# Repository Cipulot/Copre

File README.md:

# Copre
 40% Topre you can do whatever you want with.

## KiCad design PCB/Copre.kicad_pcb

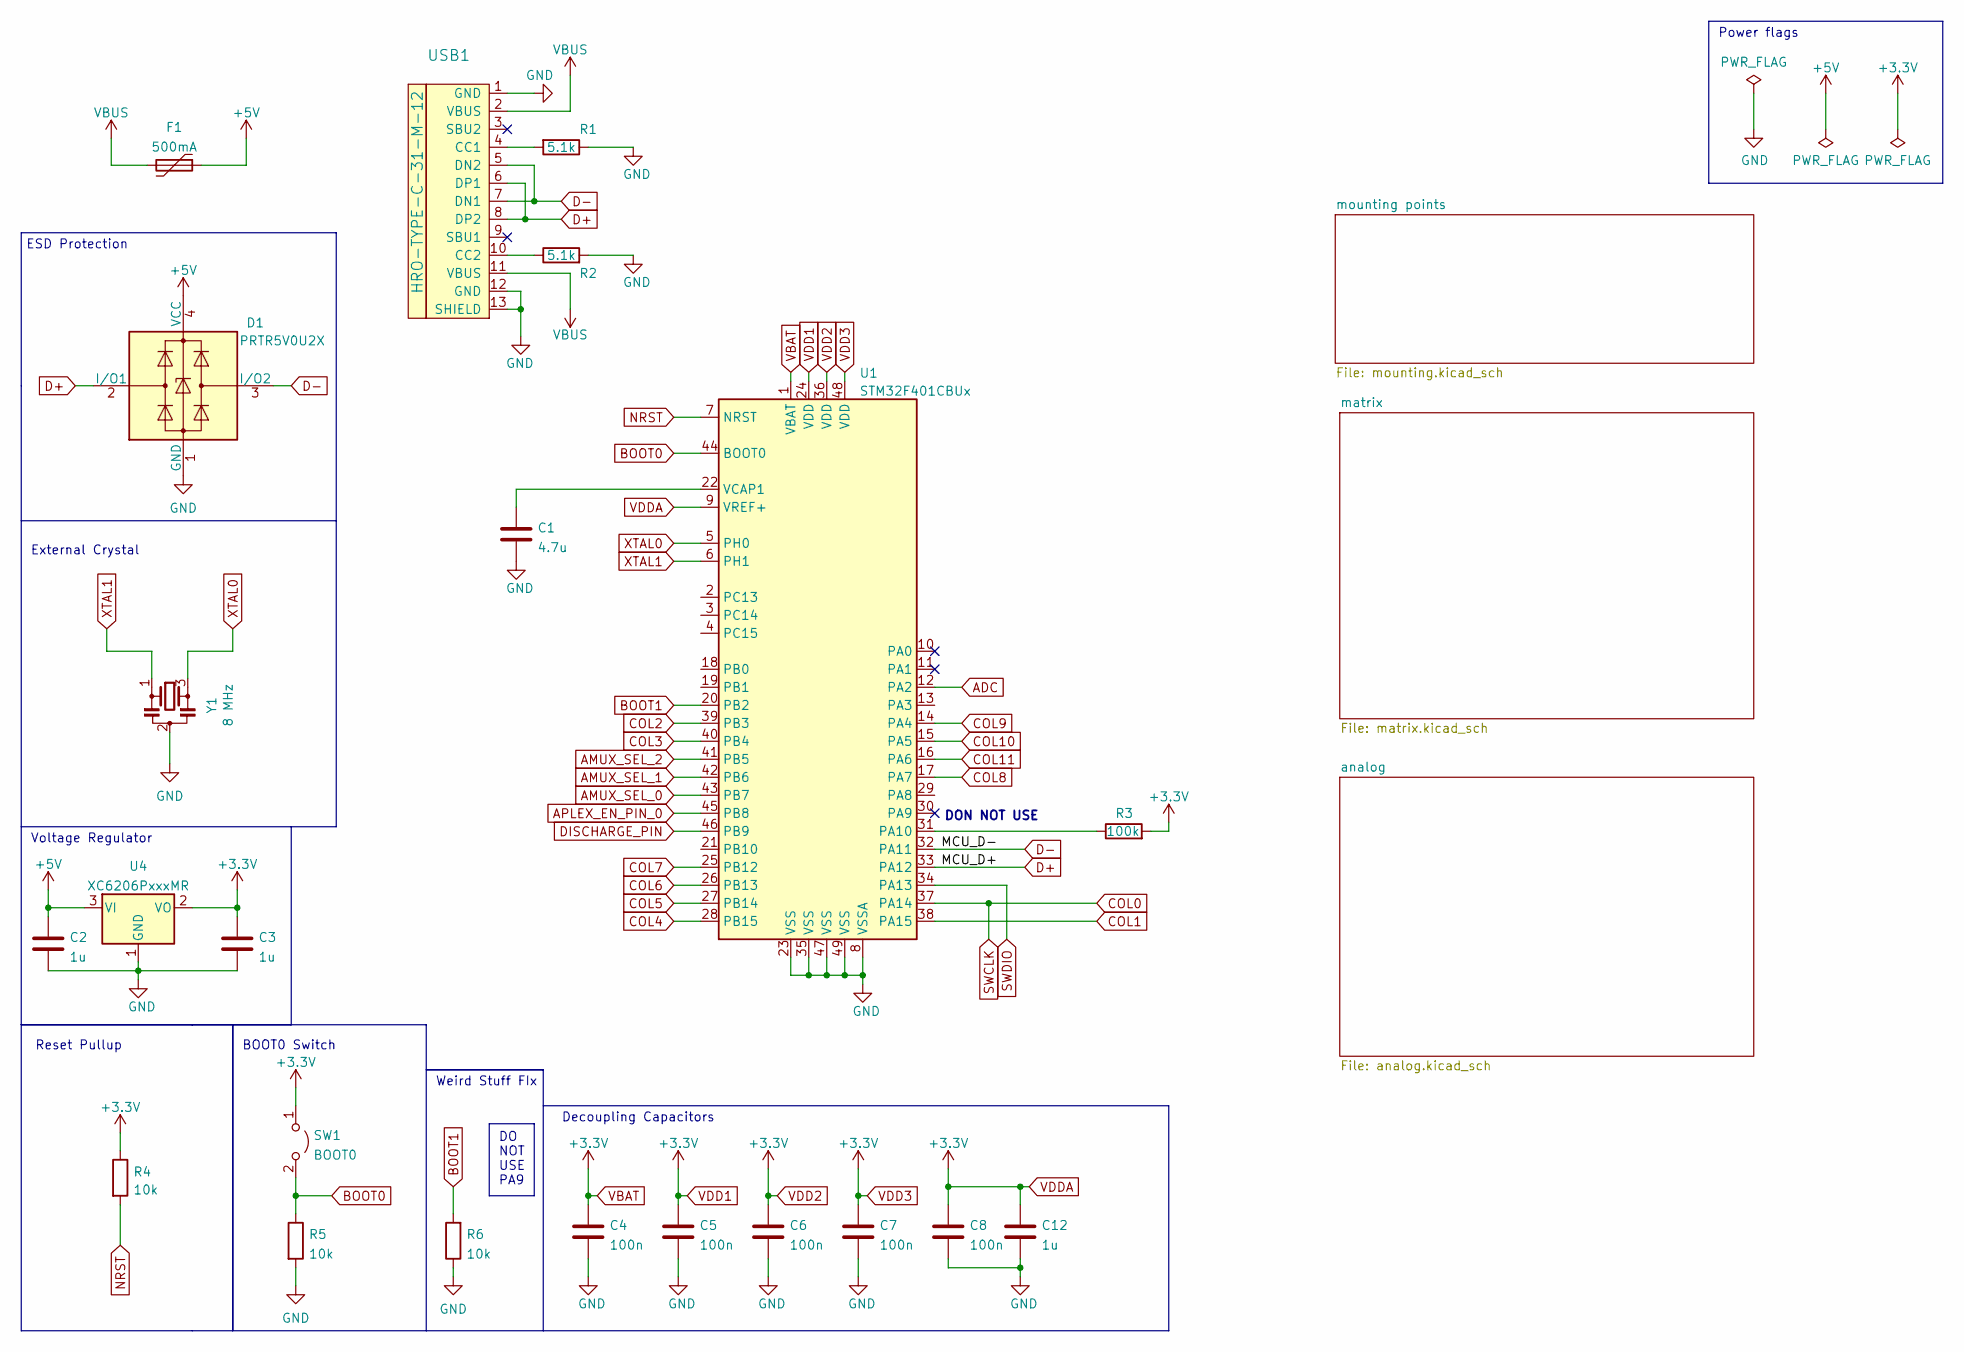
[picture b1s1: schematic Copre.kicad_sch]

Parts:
C1: 4.7u; C_0402_1005Metric; LCSC C23733
C2, C3, C12: 1u; C_0402_1005Metric; LCSC C52923
C4, C5, C6, C7, C8: 100n; C_0402_1005Metric; LCSC C307331
D1: PRTR5V0U2X; SOT-143; LCSC C2827688
F1: 500mA; Fuse_0603_1608Metric; LCSC C720073
R1, R2: 5.1k; R_0402_1005Metric; LCSC C25905
R3: 100k; R_0402_1005Metric; LCSC C25741
R4, R5, R6: 10k; R_0402_1005Metric; LCSC C25744
SW1: BOOT0; JUMPER_SMD_2DUB
U1: STM32F401CBUx; QFN-48-1EP_7x7mm_P0.5mm_EP5.6x5.6mm; LCSC C118825
U4: XC6206PxxxMR; SOT-23; LCSC C5446
USB1: HRO-TYPE-C-31-M-12; HRO-TYPE-C-31-M-12-Assembly
Y1: 8 MHz; Resonator_SMD_Murata_CSTxExxV-3Pin_3.0x1.1mm; LCSC C907975

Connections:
+5V: C2.1, D1.4 (VCC), F1.1, U4.3 (VI)
ADC: U1.12 (PA2); also elsewhere on the board
AMUX_SEL_0: U1.43 (PB7); also elsewhere on the board
AMUX_SEL_1: U1.42 (PB6); also elsewhere on the board
AMUX_SEL_2: U1.41 (PB5); also elsewhere on the board
APLEX_EN_PIN_0: U1.45 (PB8); also elsewhere on the board
APLEX_OUT_PIN_0: U1.46 (PB9); also elsewhere on the board
BOOT0: R5.1, SW1.2 (B), U1.44 (BOOT0)
BOOT1: R6.2, U1.20 (PB2)
COL0: U1.37 (PA14); also elsewhere on the board
COL1: U1.38 (PA15); also elsewhere on the board
COL2: U1.39 (PB3); also elsewhere on the board
COL3: U1.40 (PB4); also elsewhere on the board
COL4: U1.28 (PB15); also elsewhere on the board
COL5: U1.27 (PB14); also elsewhere on the board
COL6: U1.26 (PB13); also elsewhere on the board
COL7: U1.25 (PB12); also elsewhere on the board
COL8: U1.17 (PA7); also elsewhere on the board
COL9: U1.14 (PA4); also elsewhere on the board
COL10: U1.15 (PA5); also elsewhere on the board
COL11: U1.16 (PA6); also elsewhere on the board
D+: D1.2 (I/O1), U1.33 (PA12), USB1.6 (DP1), USB1.8 (DP2)
D-: D1.3 (I/O2), U1.32 (PA11), USB1.5 (DN2), USB1.7 (DN1)
GND: C1.2, C2.2, C3.2, C4.2, C5.2, C6.2, C7.2, C8.2, C12.2, D1.1 (GND), R1.1, R2.2, R5.2, R6.1, U1.8 (VSSA), U1.23 (VSS), U1.35 (VSS), U1.47 (VSS), U1.49 (VSS), U4.1 (GND), USB1.1 (GND), USB1.12 (GND), USB1.13 (SHIELD), Y1.2; also elsewhere on the board
NRST: R4.2, U1.7 (NRST)
unnamed: C1.1, U1.22 (VCAP1)
unnamed: R1.2, USB1.4 (CC1)
unnamed: R2.1, USB1.10 (CC2)
unnamed: R3.1, U1.31 (PA10)
SWDIO: U1.34 (PA13)
VBAT: C3.1, C4.1, C5.1, C6.1, C7.1, C8.1, C12.1, R3.2, R4.1, SW1.1 (A), U1.1 (VBAT), U1.9 (VREF+), U1.24 (VDD), U1.36 (VDD), U1.48 (VDD), U4.2 (VO); also elsewhere on the board
VBUS: F1.2, USB1.2 (VBUS), USB1.11 (VBUS)
XTAL0: U1.5 (PH0), Y1.3
XTAL1: U1.6 (PH1), Y1.1

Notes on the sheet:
DO NOT USE PA9
Voltage Regulator
DON NOT USE
BOOT0 Switch
External Crystal
Weird Stuff FIx
Decoupling Capacitors
Power flags
ESD Protection
Reset Pullup

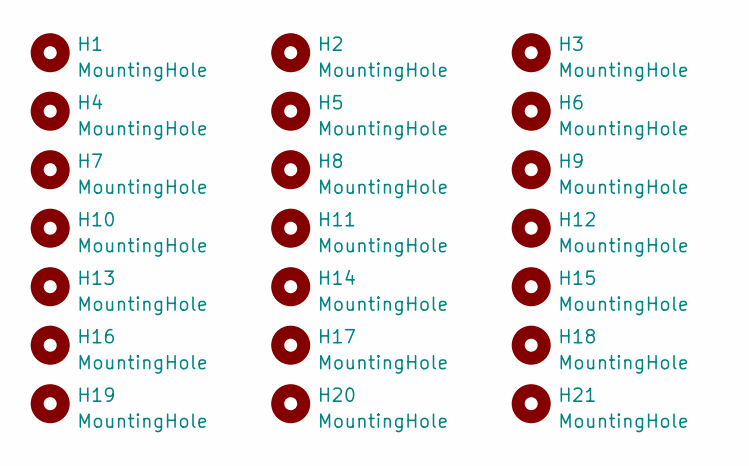
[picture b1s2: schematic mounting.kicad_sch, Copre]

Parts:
H1, H2, H3, H4, H5, H6, H7, H8, H9, H10, H11, H12, H13, H14, H15, H16, H17, H18, H19, H20, H21: MountingHole; HOLE_M2

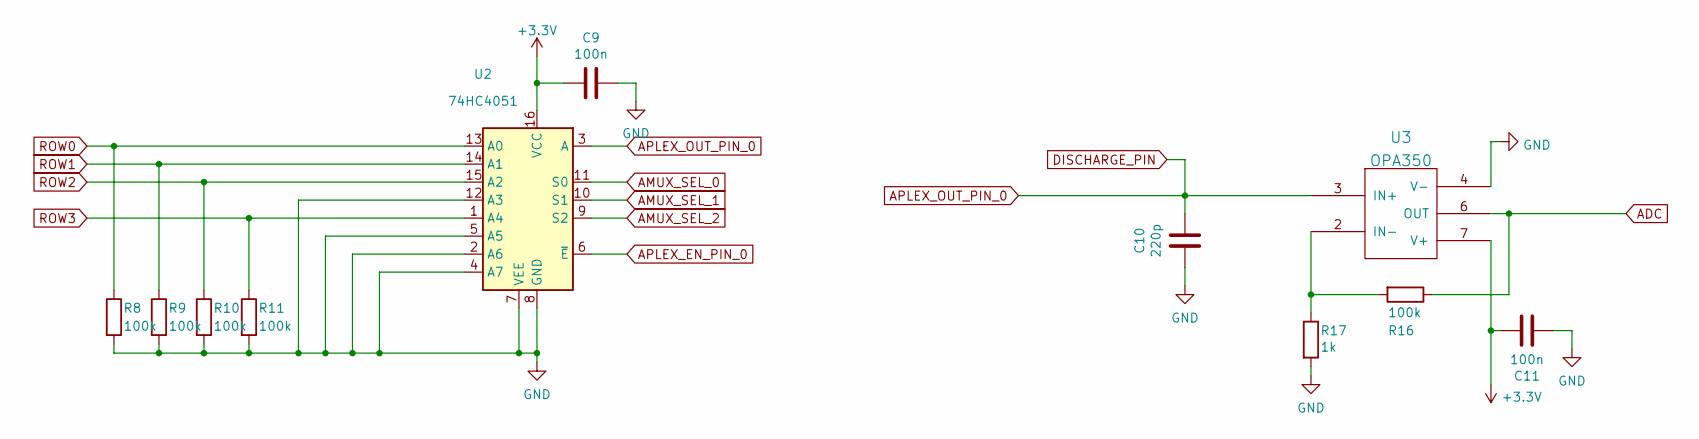
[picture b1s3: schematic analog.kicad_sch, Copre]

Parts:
C9, C11: 100n; C_0402_1005Metric; LCSC C307331
C10: 220p; C_0402_1005Metric; LCSC C1530
R8, R9, R10, R11, R16: 100k; R_0402_1005Metric; LCSC C25741
R17: 1k; R_0402_1005Metric; LCSC C11702
U2: 74HC4051; TSSOP16; LCSC C5645
U3: OPA350; VSSOP-8_3.0x3.0mm_P0.65mm; LCSC C87906

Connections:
ADC: R16.1, U3.6 (OUT); also elsewhere on the board
AMUX_SEL_0: U2.11 (S0); also elsewhere on the board
AMUX_SEL_1: U2.10 (S1); also elsewhere on the board
AMUX_SEL_2: U2.9 (S2); also elsewhere on the board
APLEX_EN_PIN_0: U2.6 (~E); also elsewhere on the board
APLEX_OUT_PIN_0: C10.1, U2.3 (A), U3.3 (IN+); also elsewhere on the board
GND: C9.1, C10.2, C11.1, R8.2, R9.2, R10.2, R11.2, R17.2, U2.2 (A6), U2.4 (A7), U2.5 (A5), U2.7 (VEE), U2.8 (GND), U2.12 (A3), U3.4 (V-); also elsewhere on the board
unnamed: R16.2, R17.1, U3.2 (IN-)
ROW0: R8.1, U2.13 (A0); also elsewhere on the board
ROW1: R9.1, U2.14 (A1); also elsewhere on the board
ROW2: R10.1, U2.15 (A2); also elsewhere on the board
ROW3: R11.1, U2.1 (A4); also elsewhere on the board
VBAT: C9.2, C11.2, U2.16 (VCC), U3.7 (V+); also elsewhere on the board

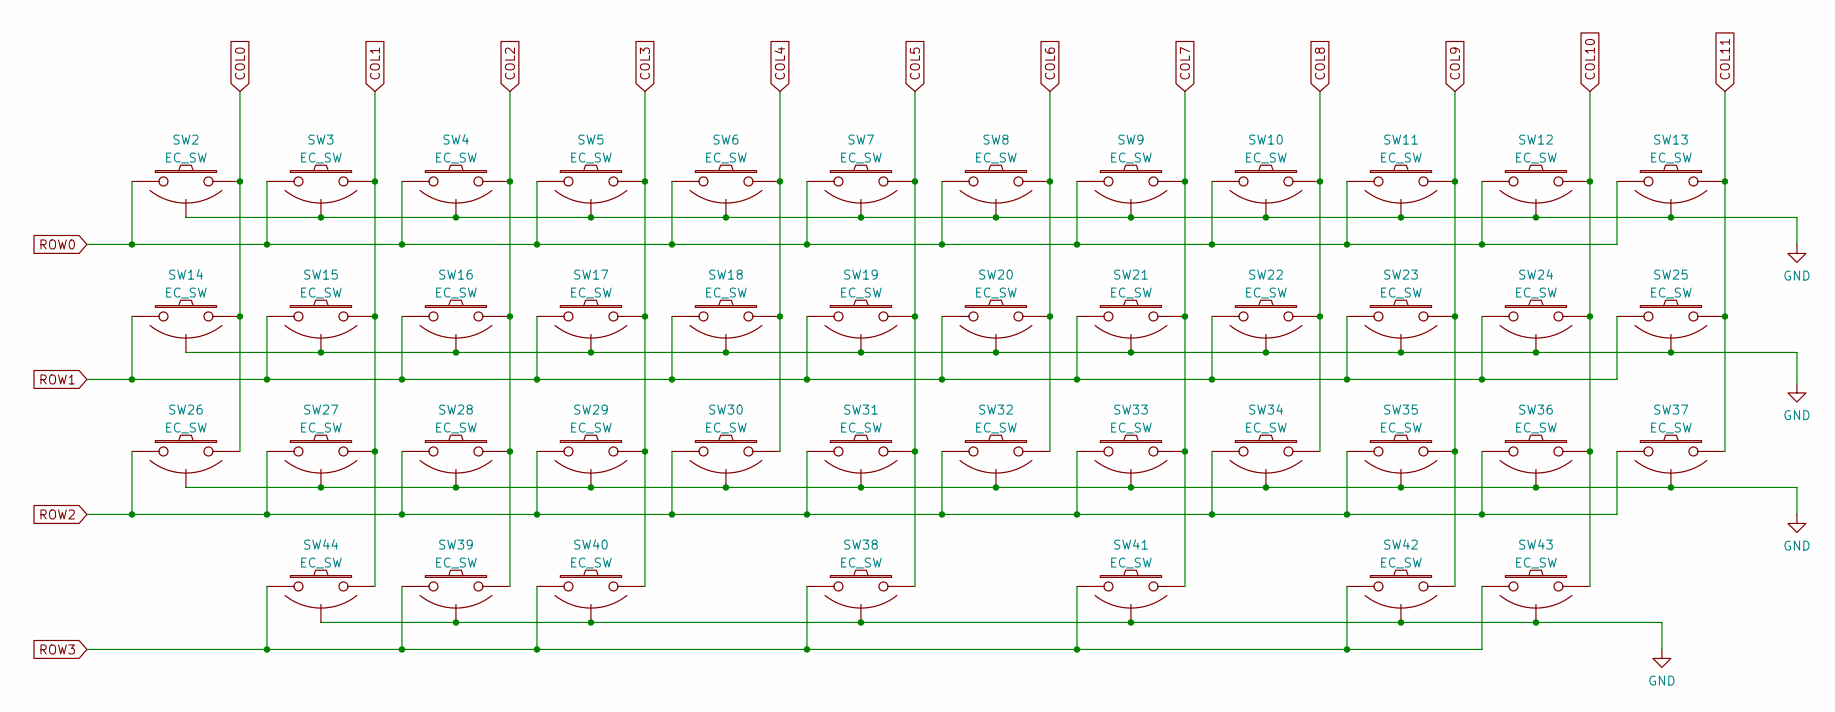
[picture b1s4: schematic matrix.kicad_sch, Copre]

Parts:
SW2, SW3, SW4, SW5, SW6, SW7, SW8, SW9, SW10, SW11, SW12, SW13, SW14, SW15, SW16, SW17, SW18, SW19, SW20, SW21, SW22, SW23, SW24, SW25, SW26, SW27, SW28, SW29, SW30, SW31, SW32, SW33, SW34, SW35, SW36, SW37, SW38, SW39, SW40, SW41, SW42: EC_SW; ecs_pad_no_ring
SW43, SW44: EC_SW; ecs_pad_no_ring_stepped&normal

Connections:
COL0: SW2.2, SW14.2, SW26.2; also elsewhere on the board
COL1: SW3.2, SW15.2, SW27.2, SW44.1; also elsewhere on the board
COL2: SW4.2, SW16.2, SW28.2, SW39.2; also elsewhere on the board
COL3: SW5.2, SW17.2, SW29.2, SW40.2; also elsewhere on the board
COL4: SW6.2, SW18.2, SW30.2; also elsewhere on the board
COL5: SW7.2, SW19.2, SW31.2, SW38.2; also elsewhere on the board
COL6: SW8.2, SW20.2, SW32.2; also elsewhere on the board
COL7: SW9.2, SW21.2, SW33.2, SW41.2; also elsewhere on the board
COL8: SW10.2, SW22.2, SW34.2; also elsewhere on the board
COL9: SW11.2, SW23.2, SW35.2, SW42.2; also elsewhere on the board
COL10: SW12.2, SW24.2, SW36.2, SW43.1; also elsewhere on the board
COL11: SW13.2, SW25.2, SW37.2; also elsewhere on the board
GND: SW2.3 (SG), SW3.3 (SG), SW4.3 (SG), SW5.3 (SG), SW6.3 (SG), SW7.3 (SG), SW8.3 (SG), SW9.3 (SG), SW10.3 (SG), SW11.3 (SG), SW12.3 (SG), SW13.3 (SG), SW14.3 (SG), SW15.3 (SG), SW16.3 (SG), SW17.3 (SG), SW18.3 (SG), SW19.3 (SG), SW20.3 (SG), SW21.3 (SG), SW22.3 (SG), SW23.3 (SG), SW24.3 (SG), SW25.3 (SG), SW26.3 (SG), SW27.3 (SG), SW28.3 (SG), SW29.3 (SG), SW30.3 (SG), SW31.3 (SG), SW32.3 (SG), SW33.3 (SG), SW34.3 (SG), SW35.3 (SG), SW36.3 (SG), SW37.3 (SG), SW38.3 (SG), SW39.3 (SG), SW40.3 (SG), SW41.3 (SG), SW42.3 (SG), SW43.3 (SG), SW44.3 (SG); also elsewhere on the board
ROW0: SW2.1, SW3.1, SW4.1, SW5.1, SW6.1, SW7.1, SW8.1, SW9.1, SW10.1, SW11.1, SW12.1, SW13.1; also elsewhere on the board
ROW1: SW14.1, SW15.1, SW16.1, SW17.1, SW18.1, SW19.1, SW20.1, SW21.1, SW22.1, SW23.1, SW24.1, SW25.1; also elsewhere on the board
ROW2: SW26.1, SW27.1, SW28.1, SW29.1, SW30.1, SW31.1, SW32.1, SW33.1, SW34.1, SW35.1, SW36.1, SW37.1; also elsewhere on the board
ROW3: SW38.1, SW39.1, SW40.1, SW41.1, SW42.1, SW43.2, SW44.2; also elsewhere on the board

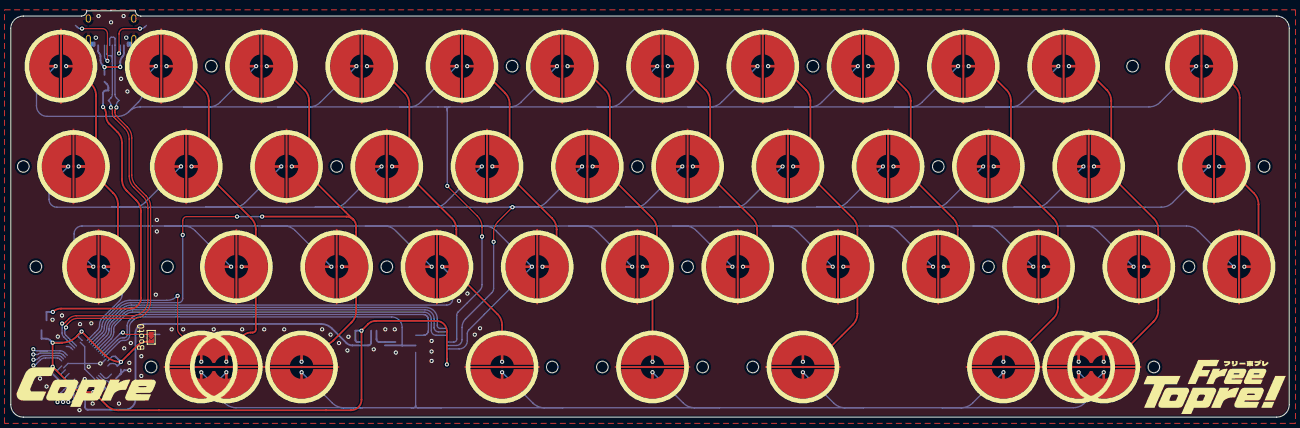
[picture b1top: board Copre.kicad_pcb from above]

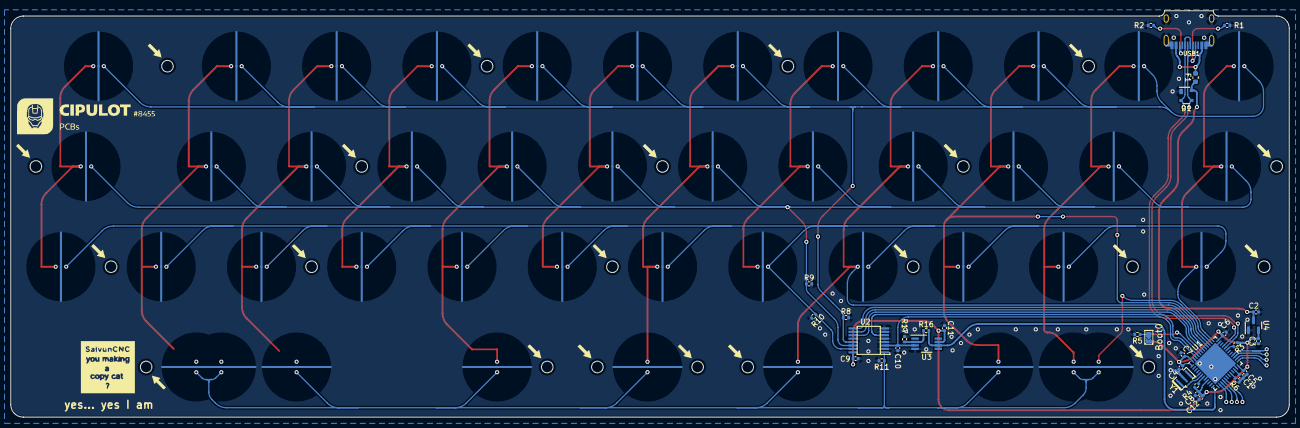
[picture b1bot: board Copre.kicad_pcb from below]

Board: 4 copper layers, 242.9 x 77.2 mm, 97 parts (32 on the bottom side), 38 nets.

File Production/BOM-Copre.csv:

Comment,Designator,Footprint,LCSC
1k,R17,R_0402_1005Metric,C11702
STM32F401CBUx,U1,QFN-48-1EP_7x7mm_P0.5mm_EP5.6x5.6mm,C118825
220p,C10,C_0402_1005Metric,C1530
HRO-TYPE-C-31-M-12,USB1,HRO-TYPE-C-31-M-12-Assembly,C165948
4.7u,C1,C_0402_1005Metric,C23733
100k,"R10,R11,R16,R3,R8,R9",R_0402_1005Metric,C25741
10k,"R4,R5,R6",R_0402_1005Metric,C25744
5.1k,"R1,R2",R_0402_1005Metric,C25905
PRTR5V0U2X,D1,SOT-143,C2827688
100n,"C11,C4,C5,C6,C7,C8,C9",C_0402_1005Metric,C307331
1u,"C12,C2,C3",C_0402_1005Metric,C52923
XC6206PxxxMR,U4,SOT-23,C5446
74HC4051,U2,TSSOP16,C5645
500mA,F1,Fuse_0603_1608Metric,C720073
OPA350,U3,VSSOP-8_3.0x3.0mm_P0.65mm,C87906
8 MHz,Y1,Resonator_SMD_Murata_CSTxExxV-3Pin_3.0x1.1mm,C907975

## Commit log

2022-10-09 PCB Dump
2022-10-09 Image Dump
2022-10-09 Create LICENSE
